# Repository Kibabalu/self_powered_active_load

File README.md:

# self_powered_active_load

Self powered active load based on the legendary LM10 Operational Amplifier and Voltage Reference IC originally designed by Bob Widlar.

Independently of the applied voltage, the circuit composed by the transistors Q3, Q4, Q5, and Q6 generates a constant voltage of 1.2V to supply the LM10 controlled by the LM10 reference buffer itself. Thus, it is controlling its own supply voltage. Q3, Q4, and Q5 are composing a current mirror and Q6 is the final control element. This works down to an applied voltage of 2V. The transistors Q1 and Q2 are forming a constant current source to drive a power-on-LED independently from the applied voltage.

The main function of the circuit, the load current control, is done by the remaining precision operational amplifier. Four Sziklai-like output stages functions as final control elements for the current load.

For the heat to be dissipated, an appropriate heat sink is needed. Here the sink LA 6 from Fischer Elektronik with a length of 150mm is used. The sink can be optionally equipped with a fan. This can increases the maximum allowed power a lot.

The specs are roughly
- Voltage: It starts down at 2V and goes up to 60V. Technically the upper border goes up to 100V due to the chosen transistor BDW93CFP for the output stages. **But it's not recommended to leave the safe area of safety-low voltages**, in particular for amateurs. Stay always inside the field covered up by your knowledge and expierences!
- Max current: Each of the four Sziklai-like output stages with their shunt resistors can stand approx. 2.5A. Thus, overall 10A load current should be fine. For higher load currents the base circuit could be scaled by adding more output stages.
- Max power: 30W without fan / 100W with fan

Production data, including the gerber files, can be found in the subfolder _production_. Or feel free to use the source files for your own projects.

The Circuit is mainly adopted from the source: Joel Setton; _Precision active load operates as low as 2V_, EDN, 2005. There's also a commercial version based on the same original circuit available: The TekBox TBOH02 self powered load.

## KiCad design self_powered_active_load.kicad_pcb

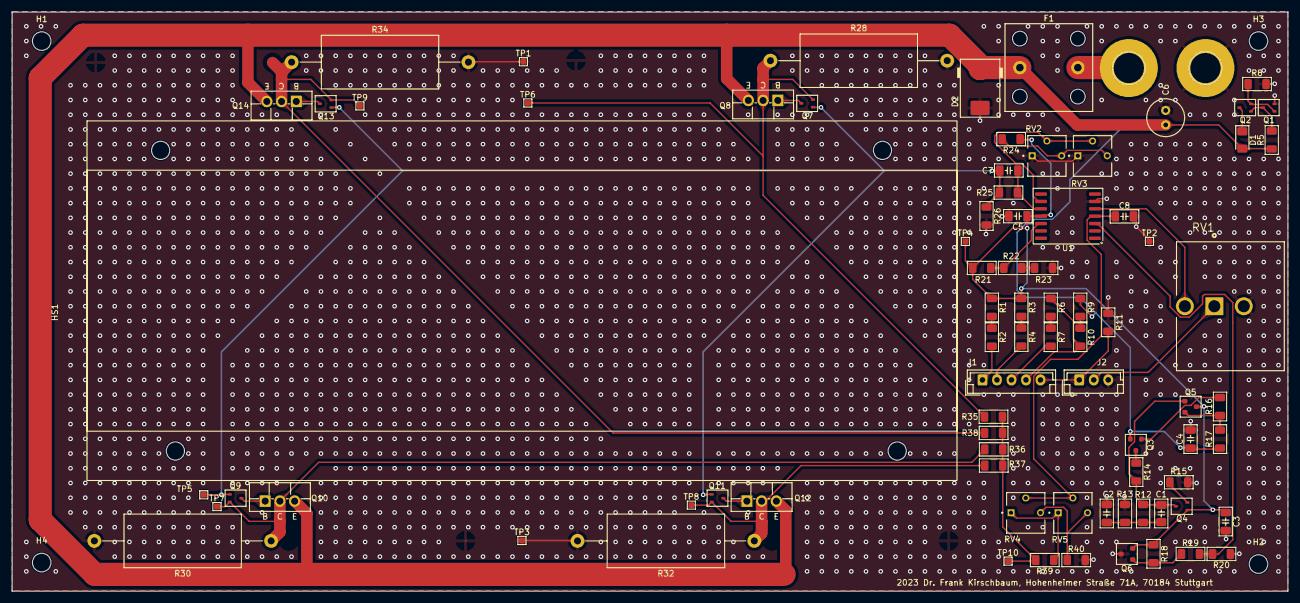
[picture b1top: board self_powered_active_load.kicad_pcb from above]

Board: 2 copper layers, 220.0 x 99.8 mm, 86 parts (0 on the bottom side), 44 nets.

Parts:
C1: 100n; C_1206_3216Metric_Pad1.42x1.75mm_HandSolder
C2, C5, C7: 100n; C_1206_3216Metric_Pad1.33x1.80mm_HandSolder
C3, C4: 1u; C_1206_3216Metric_Pad1.33x1.80mm_HandSolder
C6: 10u; C_Radial_D6.3mm_H11.0mm_P2.50mm
C8: 10u; C_1206_3216Metric_Pad1.33x1.80mm_HandSolder
D1: LED; LED_1206_3216Metric_Pad1.42x1.75mm_HandSolder
D2: SMCJ54A; D_SMC
F1: Fuse; Fuseholder_Cylinder-5x20mm_EATON_HBV_Vertical_Closed
H1, H2, H3, H4: MountingHole; MountingHole_3.2mm_M3_DIN965
HS1: Heatsink; Fischer_Heatsink_LA6_150
J1: Conn_01x05; JST_EH_B5B-EH-A_1x05_P2.50mm_Vertical
J2: Conn_01x03; JST_EH_B3B-EH-A_1x03_P2.50mm_Vertical
J3, J4: BANANA_CONN
Q1, Q2, Q4, Q7, Q9, Q11, Q13: 2SC4117; SOT-323_SC-70
Q3, Q5, Q6: MMBT5401; SOT-23
Q8, Q10, Q12, Q14: BDW94CFP; TO-220F-3_Vertical_BCE
R1, R26: 6k8; R_1206_3216Metric_Pad1.30x1.75mm_HandSolder
R2: 200R; R_1206_3216Metric_Pad1.30x1.75mm_HandSolder
R3, R6, R18, R21: 100k; R_1206_3216Metric_Pad1.30x1.75mm_HandSolder
R4, R7, R15: 15k; R_1206_3216Metric_Pad1.30x1.75mm_HandSolder
R5, R20, R25: 4k7; R_1206_3216Metric_Pad1.30x1.75mm_HandSolder
R8: 100R; R_1206_3216Metric_Pad1.30x1.75mm_HandSolder
R9: 68k; R_1206_3216Metric_Pad1.30x1.75mm_HandSolder
R10: 27k; R_1206_3216Metric_Pad1.30x1.75mm_HandSolder
R11, R16, R19, R22, R23: 10k; R_1206_3216Metric_Pad1.30x1.75mm_HandSolder
R12, R40: 1k; R_1206_3216Metric_Pad1.30x1.75mm_HandSolder
R13: 6M5; R_1206_3216Metric_Pad1.30x1.75mm_HandSolder
R14: 12k; R_1206_3216Metric_Pad1.30x1.75mm_HandSolder
R17: 220R; R_1206_3216Metric_Pad1.30x1.75mm_HandSolder
R24: 22k; R_1206_3216Metric_Pad1.30x1.75mm_HandSolder
R28, R30, R32, R34: 0R22; R_Axial_DIN0922_L20.0mm_D9.0mm_P30.48mm_Horizontal
R35, R36, R37, R38: 10R; R_1206_3216Metric_Pad1.30x1.75mm_HandSolder
R39: 47R; R_1206_3216Metric_Pad1.30x1.75mm_HandSolder
RV1: R_Potentiometer; TRIM_3590S-2-103L
RV2, RV5: 100R; TRIM_3362P-1-102LF
RV3, RV4: 1k; TRIM_3362P-1-102LF
TP1, TP2, TP3, TP4, TP5, TP6, TP7, TP8, TP9, TP10: TestPoint; TestPoint_Pad_1.0x1.0mm
U1: LM10CWM; SOIC-14W_7.5x9mm_P1.27mm

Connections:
+1V2: C3.1, C5.1, Q4.1 (B), Q5.3 (C), Q6.2 (E), R1.1, R3.1, R18.1, R21.1, R24.1, TP4.1, U1.11 (V+)
/1A/Turn: J1.1, R2.2
/10Ohm/NTurns: J1.4, R6.1, R10.2
/100Ohm/NTurns: J1.3, R7.2
/100mA/Turn: J1.2, R4.2
/ctrl: C7.2, Q7.1 (B), Q9.1 (B), Q11.1 (B), Q13.1 (B), R25.2, R26.1, TP5.1
GNDA: C2.2, C3.2, C4.2, C5.2, C6.2, C8.2, D2.2 (A), J2.3, J4.P$1 (1), Q1.2 (E), Q6.3 (C), R8.2, R11.1, R13.2, R15.2, R20.1, R23.2, R26.2, R28.2, R30.2, R32.2, R34.2, R40.2, RV1.3, RV2.1, RV3.1, TP1.1, TP2.1, TP3.1, U1.6 (V-)
unnamed: C1.2, C2.1, R12.2, R13.1
unnamed: D1.1 (K), Q2.3 (C)
unnamed: J1.5, J2.1, R11.2
unnamed: J2.2, RV1.1
unnamed: F1.2, J3.P$1 (1)
unnamed: Q1.1 (B), Q2.2 (E), R8.1
unnamed: Q1.3 (C), Q2.1 (B), R5.2
unnamed: Q3.1 (B), R16.2
unnamed: Q3.3 (C), R14.1
unnamed: C1.1, Q4.3 (C), Q5.1 (B), R12.1, R14.2
unnamed: Q4.2 (E), R15.1
unnamed: Q5.2 (E), R16.1, R17.2
unnamed: Q6.1 (B), R18.2, R19.1
unnamed: Q7.3 (C), Q8.1 (B)
unnamed: Q7.2 (E), Q8.2 (C), R28.1, R35.1, TP6.1
unnamed: Q9.3 (C), Q10.1 (B)
unnamed: Q9.2 (E), Q10.2 (C), R30.1, R36.1, TP7.1
unnamed: Q11.3 (C), Q12.1 (B)
unnamed: Q11.2 (E), Q12.2 (C), R32.1, R37.1, TP8.1
unnamed: Q13.3 (C), Q14.1 (B)
unnamed: Q13.2 (E), Q14.2 (C), R34.1, R38.1, TP9.1
unnamed: R1.2, R2.1
unnamed: R3.2, R4.1
unnamed: R6.2, R7.1
unnamed: R9.2, R10.1
unnamed: R22.2, R23.1
unnamed: R24.2, RV2.3, RV3.3
unnamed: R35.2, R36.2, R37.2, R38.2, R39.2, TP10.1
unnamed: R39.1, RV4.1, RV5.1
unnamed: R40.1, RV4.3, RV5.3
unnamed: RV2.2, RV3.2, U1.9 (BAL)
unnamed: RV1.2, U1.5 (IN+)
unnamed: C8.1, RV4.2, RV5.2, U1.4 (IN-)
unnamed: C7.1, R25.1, U1.10 (OUT)
unnamed: R19.2, R20.2, U1.3 (REF)
unnamed: R21.2, R22.1, U1.12 (RFB)
VDC: C4.1, C6.1, D1.2 (A), D2.1 (K), F1.1, Q3.2 (E), Q8.3 (E), Q10.3 (E), Q12.3 (E), Q14.3 (E), R5.1, R9.1, R17.1

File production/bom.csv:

Designator,Footprint,Quantity,Value,LCSC Part #
"C1, C2, C5, C7",1206,4,100n,
"C3, C4",1206,2,1u,
C6,C_Radial_D6.3mm_H11.0mm_P2.50mm,1,10u,
C8,1206,1,10u,
D1,1206,1,LED,
D2,D_SMC,1,SMCJ54A,
F1,Fuseholder_Cylinder-5x20mm_EATON_HBV_Vertical_Closed,1,Fuse,
"H1, H2, H3, H4",MountingHole_3.2mm_M3_DIN965,4,MountingHole,
HS1,Fischer_Heatsink_LA6_150,1,Heatsink,
J1,JST_EH_B5B-EH-A_1x05_P2.50mm_Vertical,1,Conn_01x05,
J2,JST_EH_B3B-EH-A_1x03_P2.50mm_Vertical,1,Conn_01x03,
"J3, J4",BANANA_CONN,2,BANANA_CONN,
"Q1, Q11, Q13, Q2, Q4, Q7, Q9",SOT-323_SC-70,7,2SC4117,
"Q10, Q12, Q14, Q8",TO-220F-3_Vertical_BCE,4,BDW94CFP,
"Q3, Q5, Q6",SOT-23,3,MMBT5401,
"R1, R26",1206,2,6k8,
R10,1206,1,27k,
"R11, R16, R19, R22, R23",1206,5,10k,
"R12, R40",1206,2,1k,
R13,1206,1,6M5,
R14,1206,1,12k,
"R15, R4, R7",1206,3,15k,
R17,1206,1,220R,
"R18, R21, R3, R6",1206,4,100k,
R2,1206,1,200R,
"R20, R25, R5",1206,3,4k7,
R24,1206,1,22k,
"R27, R29, R31, R33",R_Axial_DIN0922_L20.0mm_D9.0mm_P30.48mm_Horizontal,4,DNP,
"R28, R30, R32, R34",R_Axial_DIN0922_L20.0mm_D9.0mm_P30.48mm_Horizontal,4,0R22,
"R35, R36, R37, R38",1206,4,10R,
R39,1206,1,47R,
R8,1206,1,100R,
R9,1206,1,68k,
RV1,TRIM_3590S-2-103L,1,R_Potentiometer,
"RV2, RV5",TRIM_3362P-1-102LF,2,100R,
"RV3, RV4",TRIM_3362P-1-102LF,2,1k,
"TP1, TP10, TP2, TP3, TP4, TP5, TP6, TP7, TP8, TP9",TestPoint_Pad_1.0x1.0mm,10,TestPoint,
U1,SOIC-14W_7.5x9mm_P1.27mm,1,LM10CWM,

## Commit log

2023-03-29 1st commit
2023-03-29 Readme shematics
2023-04-01 routing 1st version
2023-04-01 documentation schematics
2023-04-04 routing complete rev. A
2023-04-04 PCB picture added
2023-04-04 test points added
2023-04-04 some more documentation
2023-04-04 plots generated
2023-04-06 upper side floated with GND
2023-04-06 new 3D picture
2023-04-08 schematics documentation
2023-04-09 Name added on PCB
2023-04-09 ReadMe edited
2023-04-09 Name on PCB edited
2023-04-09 via stitching added
2023-04-09 schematics print
2023-04-09 some more detailed documentation
2023-04-09 production files added
2023-04-16 Ref A2
2023-04-17 error fixed shunts
2023-04-18 error removed shunt in PCB
